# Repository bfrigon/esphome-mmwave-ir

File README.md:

DISCLAIMER!
-----------

The idea of combining these two sensors is not mine. After watching the following video from "Everything Smart Home" channel on Youtube (https://www.youtube.com/watch?v=VEqWlOeJ2YA&t=62s), i decided to develop my own board. 

This is still a work in progress. 

Description
-----------

This is a presence detection sensor for ESPHome which combine both a PIR motion and mmWave sensor. The PIR sensor, has a faster response time to movement but lack the ability to reliably detect small movements. On the other end, the mmWave sensor is able to reliably detect the smallest movements. Standing still in front of the sensor, it will still be able to detect movement just from breathing. Since it uses radio waves, it can detect a person behind a shower curtain which the PIR is unable to do making it the prefect sensor for bathrooms. However, the initial detection when entering the room can sometime be delayed a bit, enough to be noticeable. By combining these two sensor types, we get the best of both world.

I designed the board so that the PIR sensor can be mounted either facing the same direction as the mmWave sensor but also in a downward position. This way, the enclosure can be mounted near the ceiling above the door so that the PIR can detect a person entering the bathroom without detecting someone walking by in the hallway. 

Components
----------

- DFRobot SEN0395 mmWave sensor
- PIR motion sensor
- SHT45 Temperature/humidity sensor
- ESP32-C3
- USB-C (for power only)

")

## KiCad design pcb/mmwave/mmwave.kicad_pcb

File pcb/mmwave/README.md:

### Bill of material ###

```
Date    : 2022-07-29
Doc. ID : MMIR-SCH-01
Project : Esphome Mmwave Sensor / Ir Sensor
Title   : Main Board

Part #  : MMIR-V1
REV.    : B

Components : 25
```

------------------------------------------------------------------------------------------------------------------------

| Qty | Ref.      | Description                                 | Value         | Part #            | Footprint             |
|-----|-----------|---------------------------------------------|---------------|-------------------|-----------------------|
| 1   | H5        |                                             | SF2           | -                 | SF2-SensorCap         |
| 1   | J3        | Header - Single Row - 4 Pos                 | I2C           | -                 | HDR-M-1x04            |
| 1   | J4        | Header - Single Row - 6 Pos                 | MMW_SENSOR    | -                 | HDR-M-1x06            |
| 1   | J2        | Header - Dual Row - 6 Pos                   | PROG          | -                 | HDR-M-2x03            |
| 1   | J5        | Header - Single Row - 2 Pos                 | VIN           | -                 | conn-jst:B2B-PH-K     |
| 1   | J1        | USB Connector - Type C - 16 Contacts        | -             | USB4105-GF-A      | GCT_USB4105-GF-A      |
| 1   | U1        | 600mA CMOS LDO Regulator with enable        | -             | AP7365-33ERG-13   | SOT-223               |
| 1   | U3        | PIR Motion sensor                           | -             | EKMB1310111K      | PIR-EKMB1310111K-EDGE |
| 1   | U2        | ESP32-C3 Module, 4MB SPI flash, PCB antenna | -             | ESP32-C3-WROOM-02 | ESP32-C3-WROOM        |
| 1   | U4        | Temperature and humidity sensor             | -             | SHT45-AD1B-R2     | smt-dfn:DFN4          |
| 1   | R7        | Resistor                                    | 0             | -                 | SMT-0805              |
| 2   | C3, C6    | Capacitor                                   | 100nF         | -                 | SMT-0603              |
| 5   | R3-R6, R8 | Resistor                                    | 10k           | -                 | SMT-0603              |
| 1   | C2        | Capacitor                                   | 10uF          | -                 | SMT-0805              |
| 3   | C1, C4-C5 | Capacitor                                   | 1uF           | -                 | SMT-0805              |
| 2   | R1-R2     | Resistor                                    | 5.1k          | -                 | SMT-0603              |
| 1   | Z1        | ESD Supressor                               | CDSOD323-T05C | -                 | smt:SOD-323-NP        |

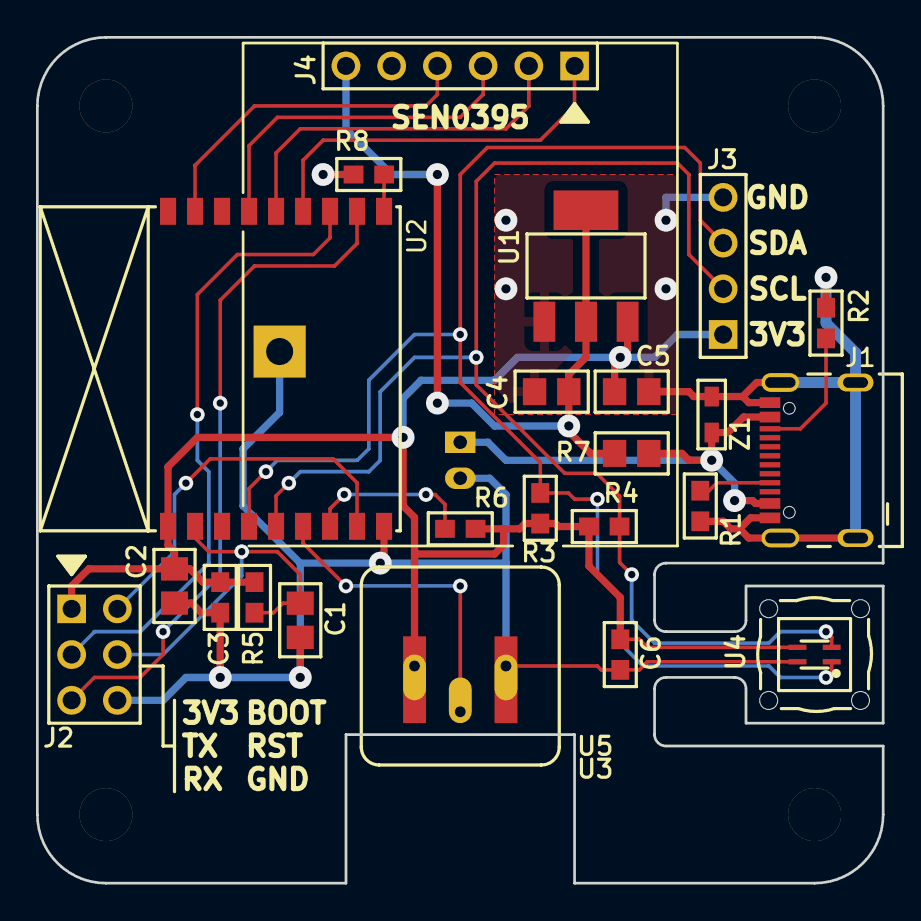
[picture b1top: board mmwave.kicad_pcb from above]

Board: 2 copper layers, 47.0 x 47.0 mm, 30 parts (1 on the bottom side), 19 nets.

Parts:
C1, C4, C5: 1uF; C-0805
C2: 10uF; C-0805
C3, C6: 100nF; C-0603
H1, H2, H3, H4: Hole; Hole-Screw-NP-#4
H5: SF2; SF2-SensorCap
J1: USB4105-GF-A; GCT_USB4105-GF-A
J2: PROG; HDR-M-2x03
J3: I2C; HDR-M-1x04
J4: MMW_SENSOR; HDR-M-1x06
J5: VIN; B2B-PH-K
R1, R2: 5.1k; R-0603
R3, R4, R5, R6, R8: 10k; R-0603
R7: 0; FER-0805
U1: AP7365-33ERG-13; SOT-223
U2: ESP32-C3-WROOM-02; ESP32-C3-WROOM
U3: EKMB1305111K; PIR-EKMB1310111K-EDGE
U4: SHT4X; DFN4
U5: N/A; PIR-EKMB1310111K
Z1: CDSOD323-T05C; SOD-323-NP

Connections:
+3V3: C2.2, C3.2, C5.2, C6.2, J2.1, J3.1, R3.2, R4.2, R5.2, R6.2, U1.3 (VOUT), U2.1 (3V3), U3.1 (VDD), U4.3 (VDD), U5.1 (VDD)
+5V: C4.2, J4.6, R7.2, U1.2 (VIN)
/BOOT: J2.2, U2.8 (IO9)
/MM_GP1: J4.3, U2.15 (IO3)
/MM_PD: J4.4, U2.17 (IO1)
/MM_RX: J4.2, U2.14 (IO19)
/MM_TX: J4.1, U2.13 (IO18)
/PIR: U2.6 (IO7), U3.2 (OUT), U5.2 (OUT)
/RESET: C1.2, J2.4, R5.1, U2.2 (EN)
/RX: J2.5, U2.11 (RXD)
/SCL: J3.2, R4.1, U2.5 (IO6), U4.2 (SCL)
/SDA: J3.3, R3.1, U2.4 (IO5), U4.1 (SDA)
/TX: J2.3, U2.12 (TXD)
GND: C1.1, C2.1, C3.1, C4.1, C5.1, C6.1, J1.G (GND), J1.SH (SHIELD), J2.6, J3.4, J4.5, J5.2, R1.1, R2.1, R8.1, U1.1 (GND), U2.9 (GND), U2.EP (GND), U3.3 (GND), U4.4 (GND), U5.3 (GND), Z1.1
unnamed: J1.A5 (CC1), R1.2
unnamed: J1.B5 (CC2), R2.2
unnamed: J1.VB (VBUS), J5.1, R7.1, Z1.2
unnamed: R6.1, U2.7 (IO8)
unnamed: R8.2, U2.10 (IO10)

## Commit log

2022-08-18 Updated BOM and schematic
2022-08-18 Add pictures
2022-08-28 Added esphome yaml
2022-08-28 Updated enclosure
